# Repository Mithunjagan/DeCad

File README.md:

<div align="center">

<picture>
<source media="(prefers-reduced-motion: reduce)" srcset="docs/media/studio-hero.svg"/>

</picture>

<br/>

**Turn scanned schematics into circuits you can inspect, refine, and export.**

A local workspace for the whole journey: source images, component review, native CAD, and the details in between.

**[Setup guide](docs/SETUP.md)** · **[Get started](#-quick-start)** · **[Explore the studio](#-product-tour)** · **[Full screenshot gallery](docs/SCREENSHOTS.md)** · **[Measured results](#-measured-not-promised)** · **[How it works](#-how-it-works)**

<br/>

<a href="docs/SCREENSHOTS.md"><picture>
<source media="(prefers-reduced-motion: reduce)" srcset="docs/screenshots/welcome.jpg"/>

</picture></a>

<sub>A little less friction. A lot more room for your next circuit. An 18-second tour of actual UI captures.</sub>

<sub><a href="docs/SCREENSHOTS.md">Explore every screen</a> · <a href="docs/screenshots/welcome.jpg">View the static welcome screen</a></sub>

</div>

---

## From a drawing to a design

Paper schematics hold years of engineering work. DeCad brings those drawings into a workspace where
you can inspect the recognized components, check physical pin connections, compare the source,
and generate a native design. Review stays part of the process, with uncertainties visible before export.

## ✨ Why DeCad

| A workspace for real circuit work | What you can inspect |
|---|---|
| **Source-aware review** | Component values, physical pin IDs, source comparisons, and explicit unresolved evidence. |
| **Native CAD output** | KiCad schematics and Capture `.DSN` files, with graph readback checks separate from recognition scores. |
| **Your component libraries** | KiCad and OrCAD sources, workspace libraries, footprint properties, and package review requirements. |
| **Measured GPU execution** | A separate CUDA OCR worker records the providers actually used by its sessions. |
| **A complete local workbench** | Projects, assistant commands, BOM, nets, electrical checks, local history, and simulation tools. |

The current production profile is pinned in `backend/pipeline_profiles.json`. Install requirements,
the separate OCR model asset, and the limits of the recorded results are described below.

## 📸 Product tour

Fresh captures of the running app · **24 October 2026** · Copper, Paper, Nebula, and Blueprint themes.
The logic-sheet views use a saved Sample 1 project; the screenshots show its actual review findings.

### Your circuit, with room to think

Projects on the left. Your design in the center. Commands and live resources on the right.
Switch into focus mode when the circuit needs the whole canvas.

### Keep the source in sight

Compare the original drawing with the saved reconstruction. Inspect the component list,
physical pin assignments, and review notes before applying changes.

<table>
<tr>
<td width="50%" valign="top"><br/><b>01 / Review the parts</b><br/><sub>References, values, and symbols remain editable.</sub></td>
<td width="50%" valign="top"><br/><b>02 / Follow the connections</b><br/><sub>Search nets and inspect each physical pin.</sub></td>
</tr>
<tr>
<td valign="top"><br/><b>03 / Know the parts</b><br/><sub>Inspect the BOM and follow supplier search links.</sub></td>
<td valign="top"><br/><b>04 / Bring your libraries</b><br/><sub>Search KiCad and OrCAD sources in one place.</sub></td>
</tr>
</table>

### A studio that feels like yours

<table>
<tr>
<td width="50%" valign="top"><br/><b>Paper</b><br/><sub>Warm surfaces and a quieter daylight workspace.</sub></td>
<td width="50%" valign="top"><br/><b>Nebula</b><br/><sub>Deep violet with luminous accents.</sub></td>
</tr>
</table>

**[Open the complete screenshot gallery →](docs/SCREENSHOTS.md)**

Welcome screens · imports · source comparison · review notes · BOM · nets · checks · source editor ·
libraries · command palette · history · applications · hardware monitor · focus mode · themes.

<!-- BEGIN GENERATED MEASUREMENTS -->
## 📊 Measured, not promised

**Recorded clear-sheet result: 228/245 labelled pin → net assignments exact (93.1%).**

Measured on **24 October 2026**, with a fresh, process-isolated CUDA OCR gate. These scores
measure recognized graphs **before CAD library substitution**. They cover four clear sheets and
selected labelled pin checkpoints, rather than complete-circuit accuracy. Later source changes
and the code-test results below do not constitute another OCR benchmark.

| Input | Matched parts / truth | Extra detections | Correct values / matched parts | Exact labelled pins | Worker time |
|---|---:|---:|---:|---:|---:|
| Sample 1 | 24/28 | 0 | 24/24 | **54/56 (96.4%)** | 159.8 s |
| Sample 3 | 30/34 | 1 | 29/30 | **63/69 (91.3%)** | 161.5 s |
| Sample 4 | 25/30 | 0 | 23/25 | **69/72 (95.8%)** | 161.4 s |
| Sample 5 | 22/25 | 0 | 21/22 | **42/48 (87.5%)** | 287.2 s |
| Sample 4 · 300 dpi | 25/30 | 4 | 23/25 | **44/72 (61.1%)** | 231.3 s |
| Sample 4 · 200 dpi | 18/30 | 2 | 17/18 | **0/72 (0.0%)** | 195.0 s |
| Sample 4 · blurred | 12/30 | 3 | 12/12 | **0/72 (0.0%)** | 188.3 s |

Sample 2 has no labelled-pin denominator in this report and is excluded from the aggregate.
The 200 dpi and blurred inputs still have **0/72 exact labelled assignments**; a valid export does
not repair an unread source. Timings belong to this recorded run and are not a speed guarantee.

**Export and appearance checks are separate measurements:**

| Recorded check | Result | What it establishes |
|---|---|---|
| Observed-graph OrCAD export regression | **19/19 cases; 2,229 pin memberships** | Saved native output preserves the supplied graph; this is not fresh recognition. |
| Faculty XML closure corpus | **18/18 exports** | XML serialization/readback, including 37 explicitly provisional terminals. TD9 application import is unverified. |
| Detailed source-appearance audits | **0/3 source-faithful** | Electrical checks passed, while symbol, geometry, or junction discrepancies still need review. |
| One saved-design footprint repair | **24/24 assigned; native PCB netlisting passed** | Five suggested packages still require physical package review. This is one case, not a corpus-wide PCB certification. |

Inspect the [raw recognition report](evidence/release-20261024/recognition-report.json),
[gate](evidence/release-20261024/recognition-gate.json),
[export summary](evidence/release-20261024/native-export-summary.json), and
[measurement definitions](docs/RESULTS.md). The [machine-readable metrics](docs/data/metrics.json)
and this chart are generated from those records with `python tools/update_readme_stats.py`.

<!-- END GENERATED MEASUREMENTS -->

### Code and setup validation for this update

| Check | Verified result | Scope |
|---|---|---|
| Backend | **478 distinct passing cases; 6 skipped** | A full run plus focused reruns after two native export fixes; the full suite was not repeated after those fixes. |
| Frontend | **22/22 tests; production compilation passed** | Built in an isolated directory; standalone packaging emitted path-tracing warnings and was not deployment-tested. |
| Native setup | **15/15 prerequisite/service checks** | This installed Windows machine; a deliberately missing KiCad path was also correctly rejected. |

See the [validation receipt](evidence/release-20261024/validation.json) for commands and limits.
These checks do not replace the dated recognition measurements above or certify a clean-machine install.

## 🧠 How it works

```mermaid
flowchart LR
    A["Image / PDF / TIFF"] --> B["Page assessment<br/>raster and vector evidence"]
    B --> C["Pinned CUDA OCR<br/>labels, physical pins, wires"]
    C --> D["Circuit graph and review evidence"]
    D --> E["Human review<br/>parts, values, nets, uncertainties"]
    E --> F["Native CAD / XML writer"]
    F --> G["Read back the saved graph"]
    G --> H["Export and discrepancy reports"]
```

The pinned `hybrid_max_accuracy` pipeline combines OCR, geometric evidence, library facts,
and bounded regional model requests where configured. Its primary and fallback regional
endpoints are defined in `backend/pipeline_profiles.json`; availability does not establish accuracy.
The reviewed graph feeds the exporters. Source geometry and native pin connectivity have
separate audits, so an electrical pass can still carry visible drawing discrepancies.

| Stage | Source |
|---|---|
| Pinned configuration and checkpoint digest | `backend/pipeline_profiles.json`, `backend/app/pipeline_profile.py` |
| Raster/vector interpretation and physical pins | `backend/app/digital_vision.py`, `backend/app/ingestion.py` |
| Isolated OCR runtime and provider verification | `backend/app/ocr_runtime.py`, `backend/app/ocr_worker.py` |
| Native Capture writing and readback | `backend/app/orcad_capture.py`, `backend/app/orcad_writer.tcl` |
| Observed graph export and package review | `backend/app/observed_export.py` |
| Source wires, symbols, and appearance audit | `backend/app/orcad_source_wires.py`, `backend/app/orcad_source_symbols.py`, `backend/app/orcad_visual_audit.py` |

## 🚀 Quick start

**[Read the complete Windows setup guide →](docs/SETUP.md)**

The published native workflow needs Windows, KiCad 10, Node.js 20.9+, a separate Python 3.12 CUDA
OCR environment, and the accepted OCR checkpoint. Native Capture output also needs your own
licensed OrCAD installation. **The code clone does not include model weights or CAD applications.**

```powershell
git clone https://github.com/Mithunjagan/DeCad.git
cd DeCad
```

Follow [the setup guide](docs/SETUP.md) to install the backend and frontend dependencies, place the
checkpoint, and configure `backend/.env` using [the example](backend/.env.example). Then:

```powershell
powershell.exe -NoProfile -ExecutionPolicy Bypass -File .\tools\check_setup.ps1 -RequireOrcad
powershell.exe -NoProfile -ExecutionPolicy Bypass -File .\start-native.ps1
```

Open **http://localhost:3100**, choose **Open local workspace**, and create a project. Try
`create a voltage divider`, then attach a source drawing for recognition. Compare the parts and
pin connections in **Review circuit**, choose an export target, and inspect the saved design's
readback and discrepancy reports. For Capture, open the design's `SCHEMATIC1 → PAGE1` page.

The guide includes custom installation paths, GPU setup, health checks, the desktop shortcut,
first conversion, and troubleshooting. The checker is read-only; it does not install software.

## ⚡ GPU-accelerated OCR

The production profile requests **CUDA**, validates the accepted ONNX checkpoint digest, and uses
a separate worker so the backend's KiCad Python keeps its own dependencies. A completed job
records the execution providers its sessions actually used. A configured worker is not proof of
GPU execution, and a strict CUDA failure does not silently turn into a CPU result.

See the [CUDA environment instructions](docs/SETUP.md#5-create-the-separate-cuda-ocr-environment).
Inspect `GET /api/vision/status` after a recognition job for the device, state, errors, and providers.
The timings in the results table belong to the recorded October 24 run; the old CPU/GPU comparison
is no longer used as the current performance headline.

## 🧰 Everything else in the box

| | |
|---|---|
| 📚 **Libraries & footprints** | Drop `.OLB` libraries, existing `.DSN` designs (their parts are extracted), Allegro/KiCad footprints, or a part map like `74F174 → soic16`. |
| 🔎 **Find any component** | Unified KiCad + OrCAD search. It acquires permitted assets, validates pin-to-pad mapping, and saves the symbol and footprint into your project. |
| 🖥️ **Native KiCad, docked** | The real `eeschema` runs inside the DeCad window, next to the project list and assistant. |
| 💬 **Assistant** | `create a voltage divider` · `add U1 74xx:74LS244` · `connect R1 pin 2 to C1 pin 1` · `run ERC` · `undo` |
| 📈 **Simulation** | ngspice, or a built-in MNA transient solver, with an oscilloscope view |
| 📦 **Exports** | KiCad · OrCAD `.DSN` · Specctra DSN (Freerouting) · EDIF · SPICE · BOM · netlists · LTspice/Qucs-S bundles |
| 🕓 **History** | Local Git commits, plus optional GitHub push |

## 🔬 Reproducing and checking results

The published numbers are backed by [dated evidence files](evidence/release-20261024/README.md).
Check their arithmetic and regenerate the README chart without running inference:

```powershell
python tools\update_readme_stats.py --check
python tools\update_readme_stats.py
```

For a new recognition run, use the installed OCR Python and a **new output directory**:

```powershell
$ocrPython = 'backend\.state\gpu-venv\Scripts\python.exe'
& $ocrPython tools\eval\profile_eval.py recognition_gate 1 3 4 5 --out evidence\my-clear-run
```

Run one GPU gate at a time. A new gate needs the input images and matching ground truth; tests
and regenerated documentation do not substitute for fresh recognition. See
[measurement definitions](docs/RESULTS.md) and [recognition configuration](docs/GENERAL_RECOGNITION.md)
for partial truth, degraded inputs, full-graph evaluation, and explicit vision mode.

For your own corpus, provide independently checked references and run:

```powershell
& $ocrPython tools\eval\run_corpus.py path\to\manifest.json --out evidence\my-corpus --mode hybrid_max_accuracy
```

The evaluator measures recognized components, exact values, physical pins, topology, false joins,
missing connections, named nets, and exact whole graphs. Incomplete references cannot establish
full-sheet accuracy. CAD export/readback and source-appearance checks remain separate.

<details>
<summary><b>⚙️ Configuration reference</b></summary>

`backend/.env` (template: `backend/.env.example`). It is git-ignored; never commit it.

| Variable | Purpose |
|---|---|
| `IMAGE_MODE` | Owned by the production `hybrid_max_accuracy` profile; explicit API recognition modes remain available |
| `S2SDN_OCR_PYTHON` / `S2SDN_OCR_DEVICE` | OCR worker Python, and `cuda` (strict), `cpu`, or unset for auto |
| `S2SDN_CUDA_DLLS` | Extra folder with CUDA 12 / cuDNN 9 DLLs |
| `S2SDN_TEXT_MODEL` | Owned by the pinned production profile and verified against its digest |
| `ORCAD_ROOT` / `S2SDN_KICAD_DIR` | OrCAD and KiCad install roots |
| `TESSERACT_DIR` | Tesseract folder, if not in a default location |
| `ALLOW_LOCAL_LOGIN` | Local workspace without GitHub sign-in |
| `GITHUB_CLIENT_ID` / `GITHUB_CLIENT_SECRET` | Optional OAuth for pushing projects |
| `OLLAMA_URL`, `CHAT_MODEL` | Optional local language model for the assistant |
| `CHAT_API_URL`, `NVIDIA_API_KEY`, `CHAT_API_MODEL` | Optional chat configuration; separate from regional recognition endpoints. Keep credentials in local environment files. |

</details>

<details>
<summary><b>🔌 HTTP API</b></summary>

The frontend reaches the backend through a same-origin `/api` proxy.

| Method | Route | Purpose |
|---|---|---|
| `POST` | `/projects/{pid}/orcad/auto` | Attachment → recognize → write → verify (`{"attachment": "references/x.jpg", "recognition_mode": "auto"}`) |
| `POST` | `/projects/{pid}/export/orcad-dsn` | Reviewed circuit JSON → verified `.DSN` zip |
| `GET` | `/projects/{pid}/orcad` | Last design status: `passed`, `checked_pins`, `corrections`, `footprints`, … |
| `GET` | `/projects/{pid}/orcad/preview.svg` · `/orcad/netlist` · `/orcad/download` | Preview, physical netlist, design zip |
| `POST` | `/projects/{pid}/orcad/open` | Open in the installed Capture |
| `GET` | `/vision/status` | Recognizer mode and verified OCR runtime |
| `POST` | `/ai/chat` | Assistant with attachments and `recognition_mode` |
| `POST` | `/library/upload` | Add `.OLB` / `.DSN` / footprints / part map / zip |
| `GET` | `/components/search` | Unified component search |

Full list: `backend/app/main.py`.

</details>

<details>
<summary><b>🗂️ Repository layout</b></summary>

```text
backend/app/      FastAPI app, recognizers, GPU worker, OrCAD Tcl scripts, libraries
backend/tests/    pytest suite
frontend/app/     Next.js 16 / React 19 workbench
desktop/ bridge/  native Windows host (docked KiCad, WebView2) and desktop bridge
checkpoints/      schematic-ocr (CRNN, ONNX + PyTorch) · circuit-lora (experimental VLM adapter)
samples/orcad/    the five evaluation schematics
tools/eval/       ground truth, scorer, degraded-scan generator, gates, results
training/         CRNN and LoRA training (local GPU + Colab notebooks)
docs/media/       README graphics
docs/data/        generated measurement summaries
docs/SETUP.md     native installation and troubleshooting
evidence/release-20261024/  published measurement receipts
```

</details>

<details>
<summary><b>🐳 Docker (without OrCAD)</b></summary>

Docker configuration remains in the repository, but the current containers do not package the
complete pinned checkpoint/CUDA profile. Docker and CPU-only startup have not been validated for
this release. Use the [native Windows setup guide](docs/SETUP.md) for the published workflow.

The historical container entry points are `start.command` and `start.ps1`.
They are not the verified native launcher.

Ports: 3100 (workbench), 8100 (API), 6180 (embedded KiCad), and optionally 11434 (Ollama).

</details>

<details>
<summary><b>🧪 Development and tests</b></summary>

```powershell
$env:KICAD_CLI = 'D:\KICAD\bin\kicad-cli.exe'
$env:KICAD_SYMBOL_DIR = 'D:\KICAD\share\kicad\symbols'
$env:KICAD_FOOTPRINT_DIR = 'D:\KICAD\share\kicad\footprints'
Push-Location backend
& .venv\Scripts\python.exe -m pytest tests -q
Pop-Location
Push-Location frontend
npm test
npm run build
Pop-Location
```

Configure the installed CAD paths before running integration tests. Use the dated recognition
gates for image-interpretation claims; code tests alone do not measure OCR accuracy.

</details>

## 🤖 Models and runtime boundaries

| Component | Role |
|---|---|
| RapidOCR / ONNX Runtime | Text detection and reading; the production worker verifies CUDA session execution. |
| Accepted schematic CRNN checkpoint | Second reader for schematic text; separately supplied, pinned by SHA-256, and not changed by this repository update. |
| Regional vision readers | Optional bounded requests configured in `backend/pipeline_profiles.json`; installation and model availability are not accuracy evidence. |
| Experimental training adapters | Research artifacts described under `training/`; they do not replace the accepted production checkpoint. |

Converted AMSnet records now require independent source-image review. Parsing a SPICE netlist
does not establish that its values and physical pin connections match the paired image.

## 🧭 Roadmap

- [x] Native graph exports with saved-file readback and explicit discrepancy reports.
- [x] Reviewed component/pin graphs and preservation of provisional evidence.
- [x] CUDA OCR workers with provider verification.
- [x] Recorded 228/245 exact labelled checkpoints across four clear sheets.
- [ ] Recover unread pin assignments on blurred and 200 dpi inputs.
- [ ] Resolve source symbol, route, and junction discrepancies in the detailed visual audits.
- [ ] Verify physical package suitability beyond footprint property assignment.
- [ ] Broaden complete, independent ground truth across more drawings and circuit families.
- [ ] Validate a portable CPU/container setup for the pinned production profile.

## ⚠️ Limitations

- The clear-sheet figure covers selected labelled pins. It is not whole-circuit success, and the
  200 dpi and blurred cases remain 0/72 on this metric.
- Recognition, exported-graph readback, source appearance, and physical PCB readiness are different
  checks. Review the original drawing, unresolved evidence, and suggested packages before use.
- Production startup requires the separate accepted OCR artifact and CUDA environment. Capture
  output additionally requires Windows and your licensed local installation.
- Multi-page imports retain page-scoped identities; hierarchy and global net equivalence require review.
- Allegro binary geometry can be cataloged but is not converted into editable geometry.
- Services are intended for local use. Credentials, personal workspaces, model weights, and caches
  are excluded from this source update.

## 📖 Documentation

[Setup guide](docs/SETUP.md) · [Measured results](docs/RESULTS.md) · [Screenshot gallery](docs/SCREENSHOTS.md) · [DEMO.md](DEMO.md) (historical runbook) · [ORCAD_STATUS.md](ORCAD_STATUS.md) (historical pipeline notes) ·
[COMPONENT_LIBRARIES.md](COMPONENT_LIBRARIES.md) · [WINDOWS_VISION.md](WINDOWS_VISION.md) ·
[SPECCTRA.md](SPECCTRA.md) · [RELEASE_GATES.md](RELEASE_GATES.md) · [STATUS.md](STATUS.md) (dated log) ·
[THIRD_PARTY.md](THIRD_PARTY.md)

## 🤝 Contributing

Issues and pull requests are welcome, especially:
- new hand-transcribed ground truth sheets;
- blurred-scan pin recovery;
- support for more EDA formats.

Please measure recognition changes end-to-end with the gate before opening a PR.

<div align="center">

### ⭐ If DeCad saves you from redrawing a schematic, star the repo. It helps others find it.

<br/>

<sub>OrCAD, Capture and Allegro are trademarks of Cadence Design Systems. OrCAD itself is not distributed.
KiCad, ngspice, RapidOCR and the other components are used under their own licenses (see <a href="THIRD_PARTY.md">THIRD_PARTY.md</a>).
<b>License:</b> proprietary, all rights reserved by the authors, until an open-source license is designated.</sub>

</div>

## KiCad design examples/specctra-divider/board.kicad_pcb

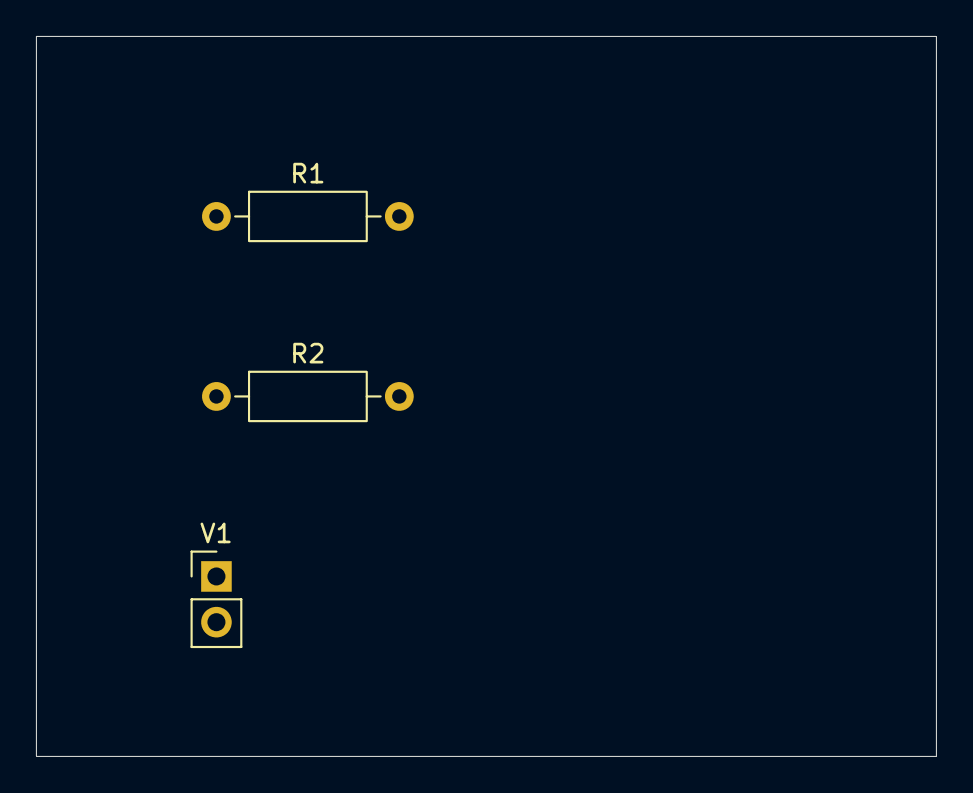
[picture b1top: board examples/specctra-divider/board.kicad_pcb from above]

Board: 2 copper layers, 50.0 x 40.0 mm, 3 parts (0 on the bottom side), 3 nets, no tracks yet.

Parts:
R1, R2: 10k; R_Axial_DIN0207_L6.3mm_D2.5mm_P10.16mm_Horizontal
V1: 5; PinHeader_1x02_P2.54mm_Vertical

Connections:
GND: R2.2, V1.2
VIN: R1.1, V1.1
VOUT: R1.2, R2.1

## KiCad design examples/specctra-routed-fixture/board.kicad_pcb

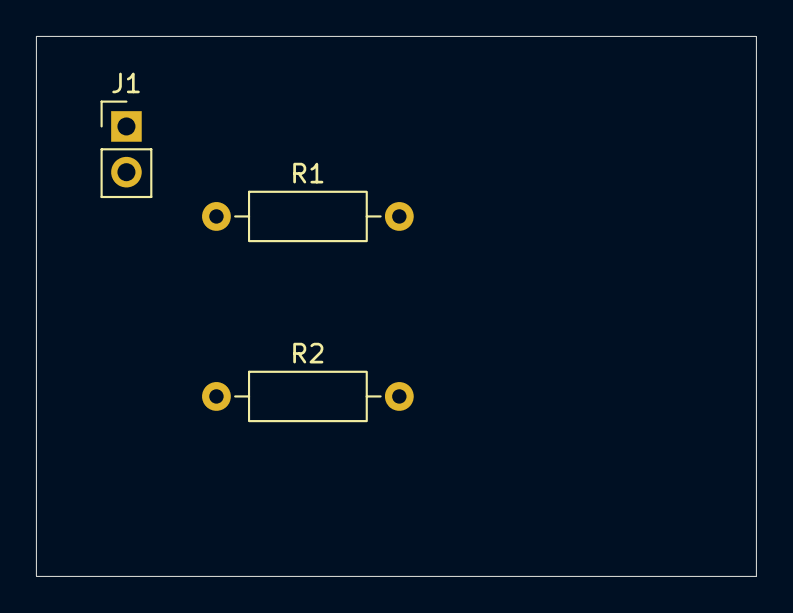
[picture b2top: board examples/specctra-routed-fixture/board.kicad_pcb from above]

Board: 2 copper layers, 40.0 x 30.0 mm, 3 parts (0 on the bottom side), 3 nets, no tracks yet.

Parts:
J1: Input; PinHeader_1x02_P2.54mm_Vertical
R1, R2: 10k; R_Axial_DIN0207_L6.3mm_D2.5mm_P10.16mm_Horizontal

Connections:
GND: J1.2, R2.2
OUT: R1.2, R2.1
VIN: J1.1, R1.1
